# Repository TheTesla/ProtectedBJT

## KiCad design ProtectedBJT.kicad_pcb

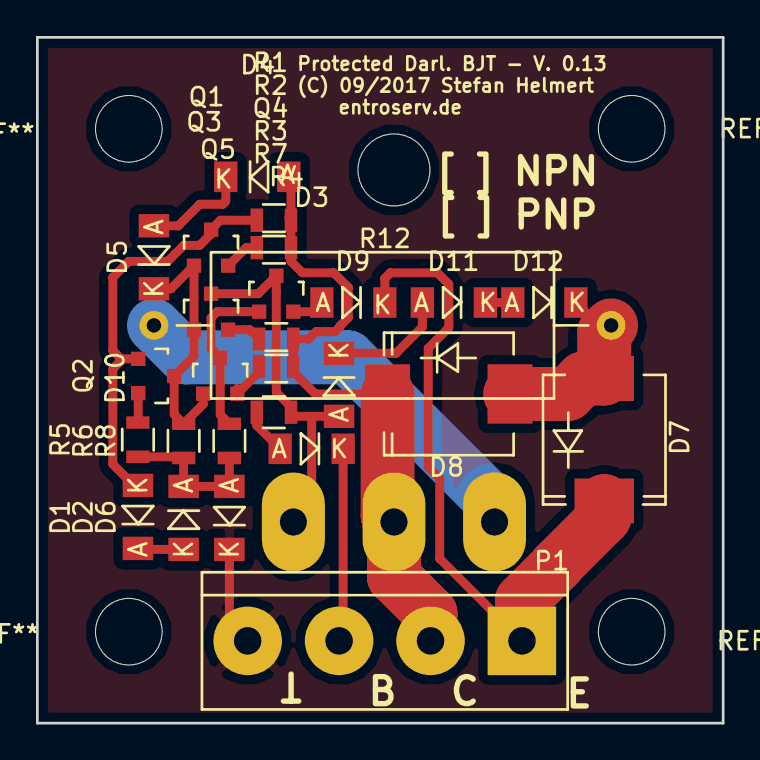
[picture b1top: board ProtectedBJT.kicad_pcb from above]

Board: 2 copper layers, 38.1 x 38.1 mm, 28 parts (1 on the bottom side), 21 nets.

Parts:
D1, D2, D3, D4, D5, D6, D9, D10, D11, D12: 1N4148; MiniMELF_Standard
D7: SK86C; SMC_Standard
D8: 68V; SMC_Standard
P1: CONN_01X04; bornier4
Q1, Q3, Q5: BC856; SOT-23
Q2, Q4: BC850; SOT-23
Q6: TIP141; TO-247_Horizontal_Neutral123_Reverse_largePads
R1, R6: 470k; R_0805
R2, R5: 1k; R_0805
R3, R4: 47; R_0805
R7, R8: 100; R_0805
R12: 0.3; Resistor_Ceramic_Horizontal_L19mm-W8mm-H8mm-p25mm

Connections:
GND: D6.1, P1.4
unnamed: D1.1, D2.2
unnamed: D1.2, Q1.3, Q2.1, R1.2
unnamed: D2.1, D6.2, R5.2, R6.2, R8.2
unnamed: D3.1, P1.3
unnamed: D3.2, R4.2
unnamed: D4.1, D5.2
unnamed: D4.2, D8.1, P1.2, Q6.2, R1.1, R2.1, R3.1, R7.1
unnamed: D5.1, Q1.1, Q2.3, Q3.1, Q5.1, R6.1
unnamed: D7.1, D9.1, P1.1
unnamed: D9.2, Q4.2
unnamed: D10.1, D11.2
unnamed: D10.2, Q3.3, Q4.3, Q6.1, R4.1
unnamed: D11.1, D12.2
unnamed: D7.2, D8.2, D12.1, R12.2
unnamed: Q1.2, R2.2
unnamed: Q2.2, R5.1
unnamed: Q3.2, R3.2
unnamed: Q4.1, Q5.3, R8.1
unnamed: Q5.2, R7.2
unnamed: Q6.3, R12.1

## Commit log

2017-08-12 first prototype version
2017-09-17 some changes on board
2017-09-17 completely new version wth darlington output transistor
2017-09-17 silk screen ready
2017-12-18 second produced version
2017-12-18 left top hole with more spacing
